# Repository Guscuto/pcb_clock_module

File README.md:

# pcb_clock_module
Clock Module PCB for 8 bit computer

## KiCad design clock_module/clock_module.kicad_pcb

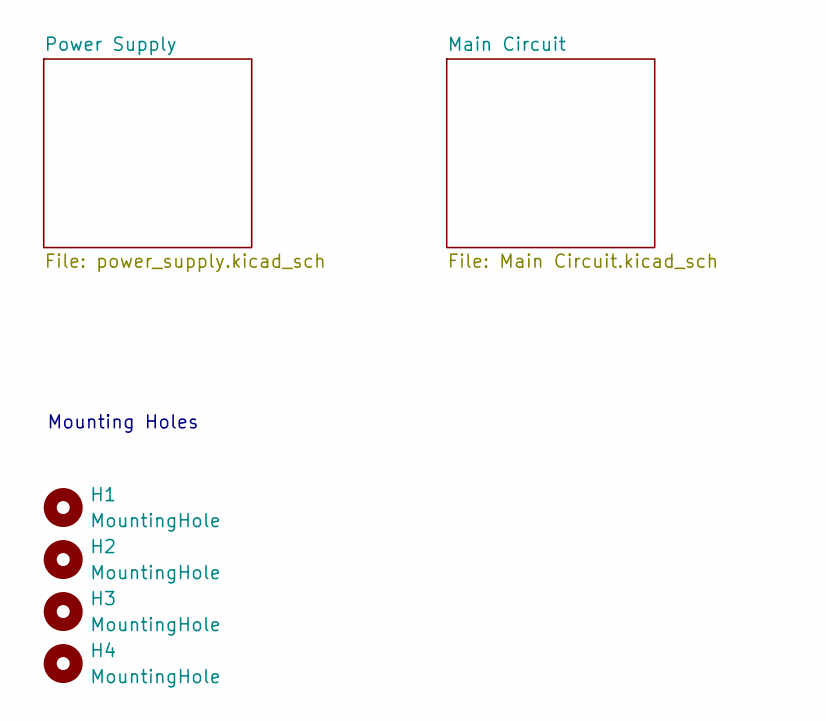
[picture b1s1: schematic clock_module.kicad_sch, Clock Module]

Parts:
H1, H2, H3, H4: MountingHole; MountingHole_3.2mm_M3

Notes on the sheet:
Mounting Holes

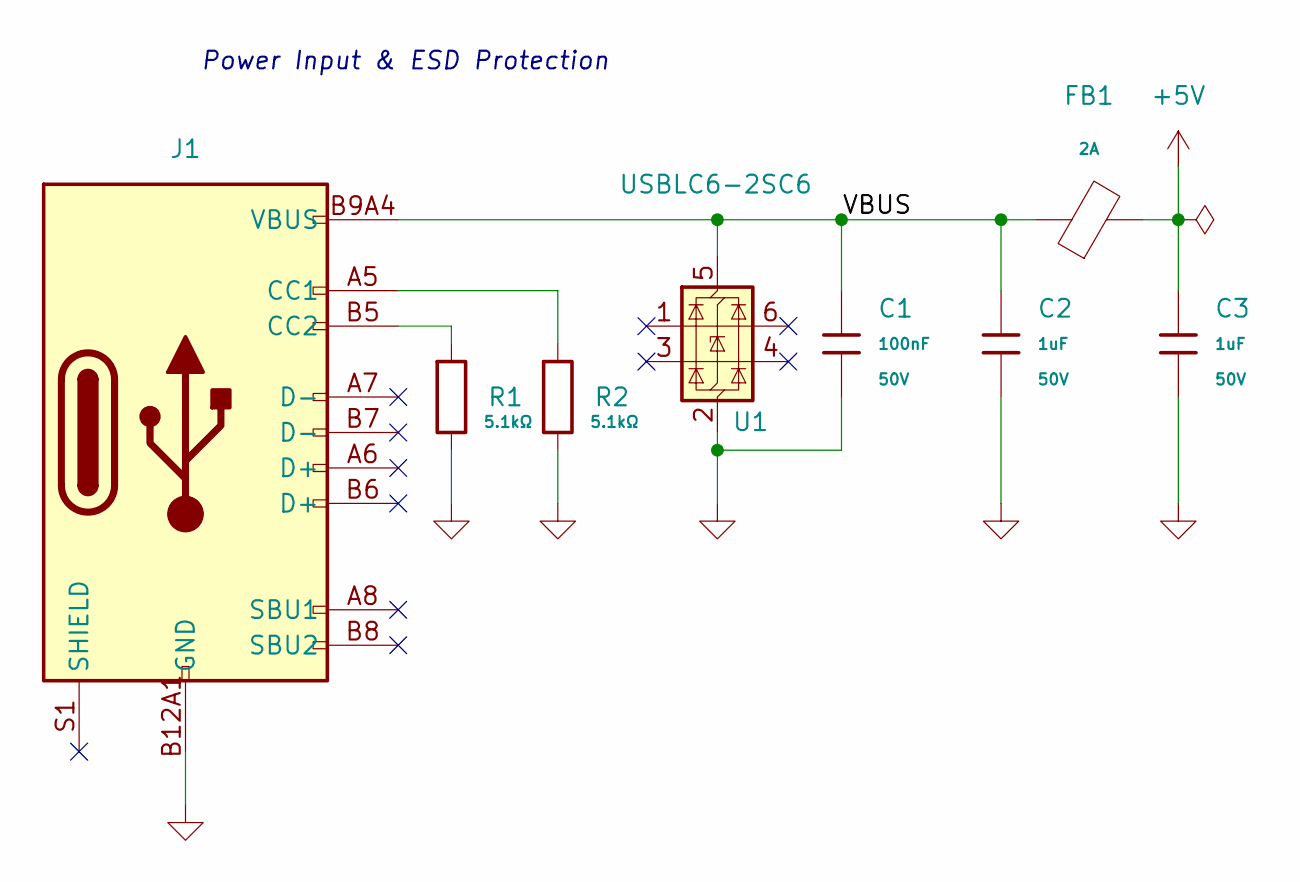
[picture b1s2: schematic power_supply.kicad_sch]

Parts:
C1: 100nF; C_0603; Voltage Rated 50V; Tolerance ±10%; Part CC0603KRX7R9BB104; LCSC C14663
C2, C3: 1uF; C_0603; Voltage Rated 50V; Tolerance ±10%; Part CL10A105KB8NNNC; LCSC C15849
FB1: FB_0603; Current Rating 2A; Tolerance ±25%; Part BLM18PG121SN1D; LCSC C14709
J1: Connector, USB-TYPE-C-16P; TYPE-C-SMD_HX-TYPE-C-16PIN; LCSC C2927039
R1, R2: 5.1kΩ; R_0603; Overload Voltage (Max) 75V; Tolerance ±1%; Part 0603WAF5101T5E; LCSC C23186
U1: USBLC6-2SC6; SOT-23-6; LCSC C7519

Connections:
+5V: C3.1, FB1.2; also elsewhere on the board
/Power Supply/VBUS: C1.1, C2.1, FB1.1, J1.A9B4 (VBUS), J1.B9A4 (VBUS), U1.5 (VBUS)
GND: C1.2, C2.2, C3.2, J1.A12B1 (GND), J1.B12A1 (GND), R1.2, R2.2, U1.2 (GND); also elsewhere on the board
unnamed: J1.A5 (CC1), R2.1
unnamed: J1.B5 (CC2), R1.1

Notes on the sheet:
Power Input & ESD Protection

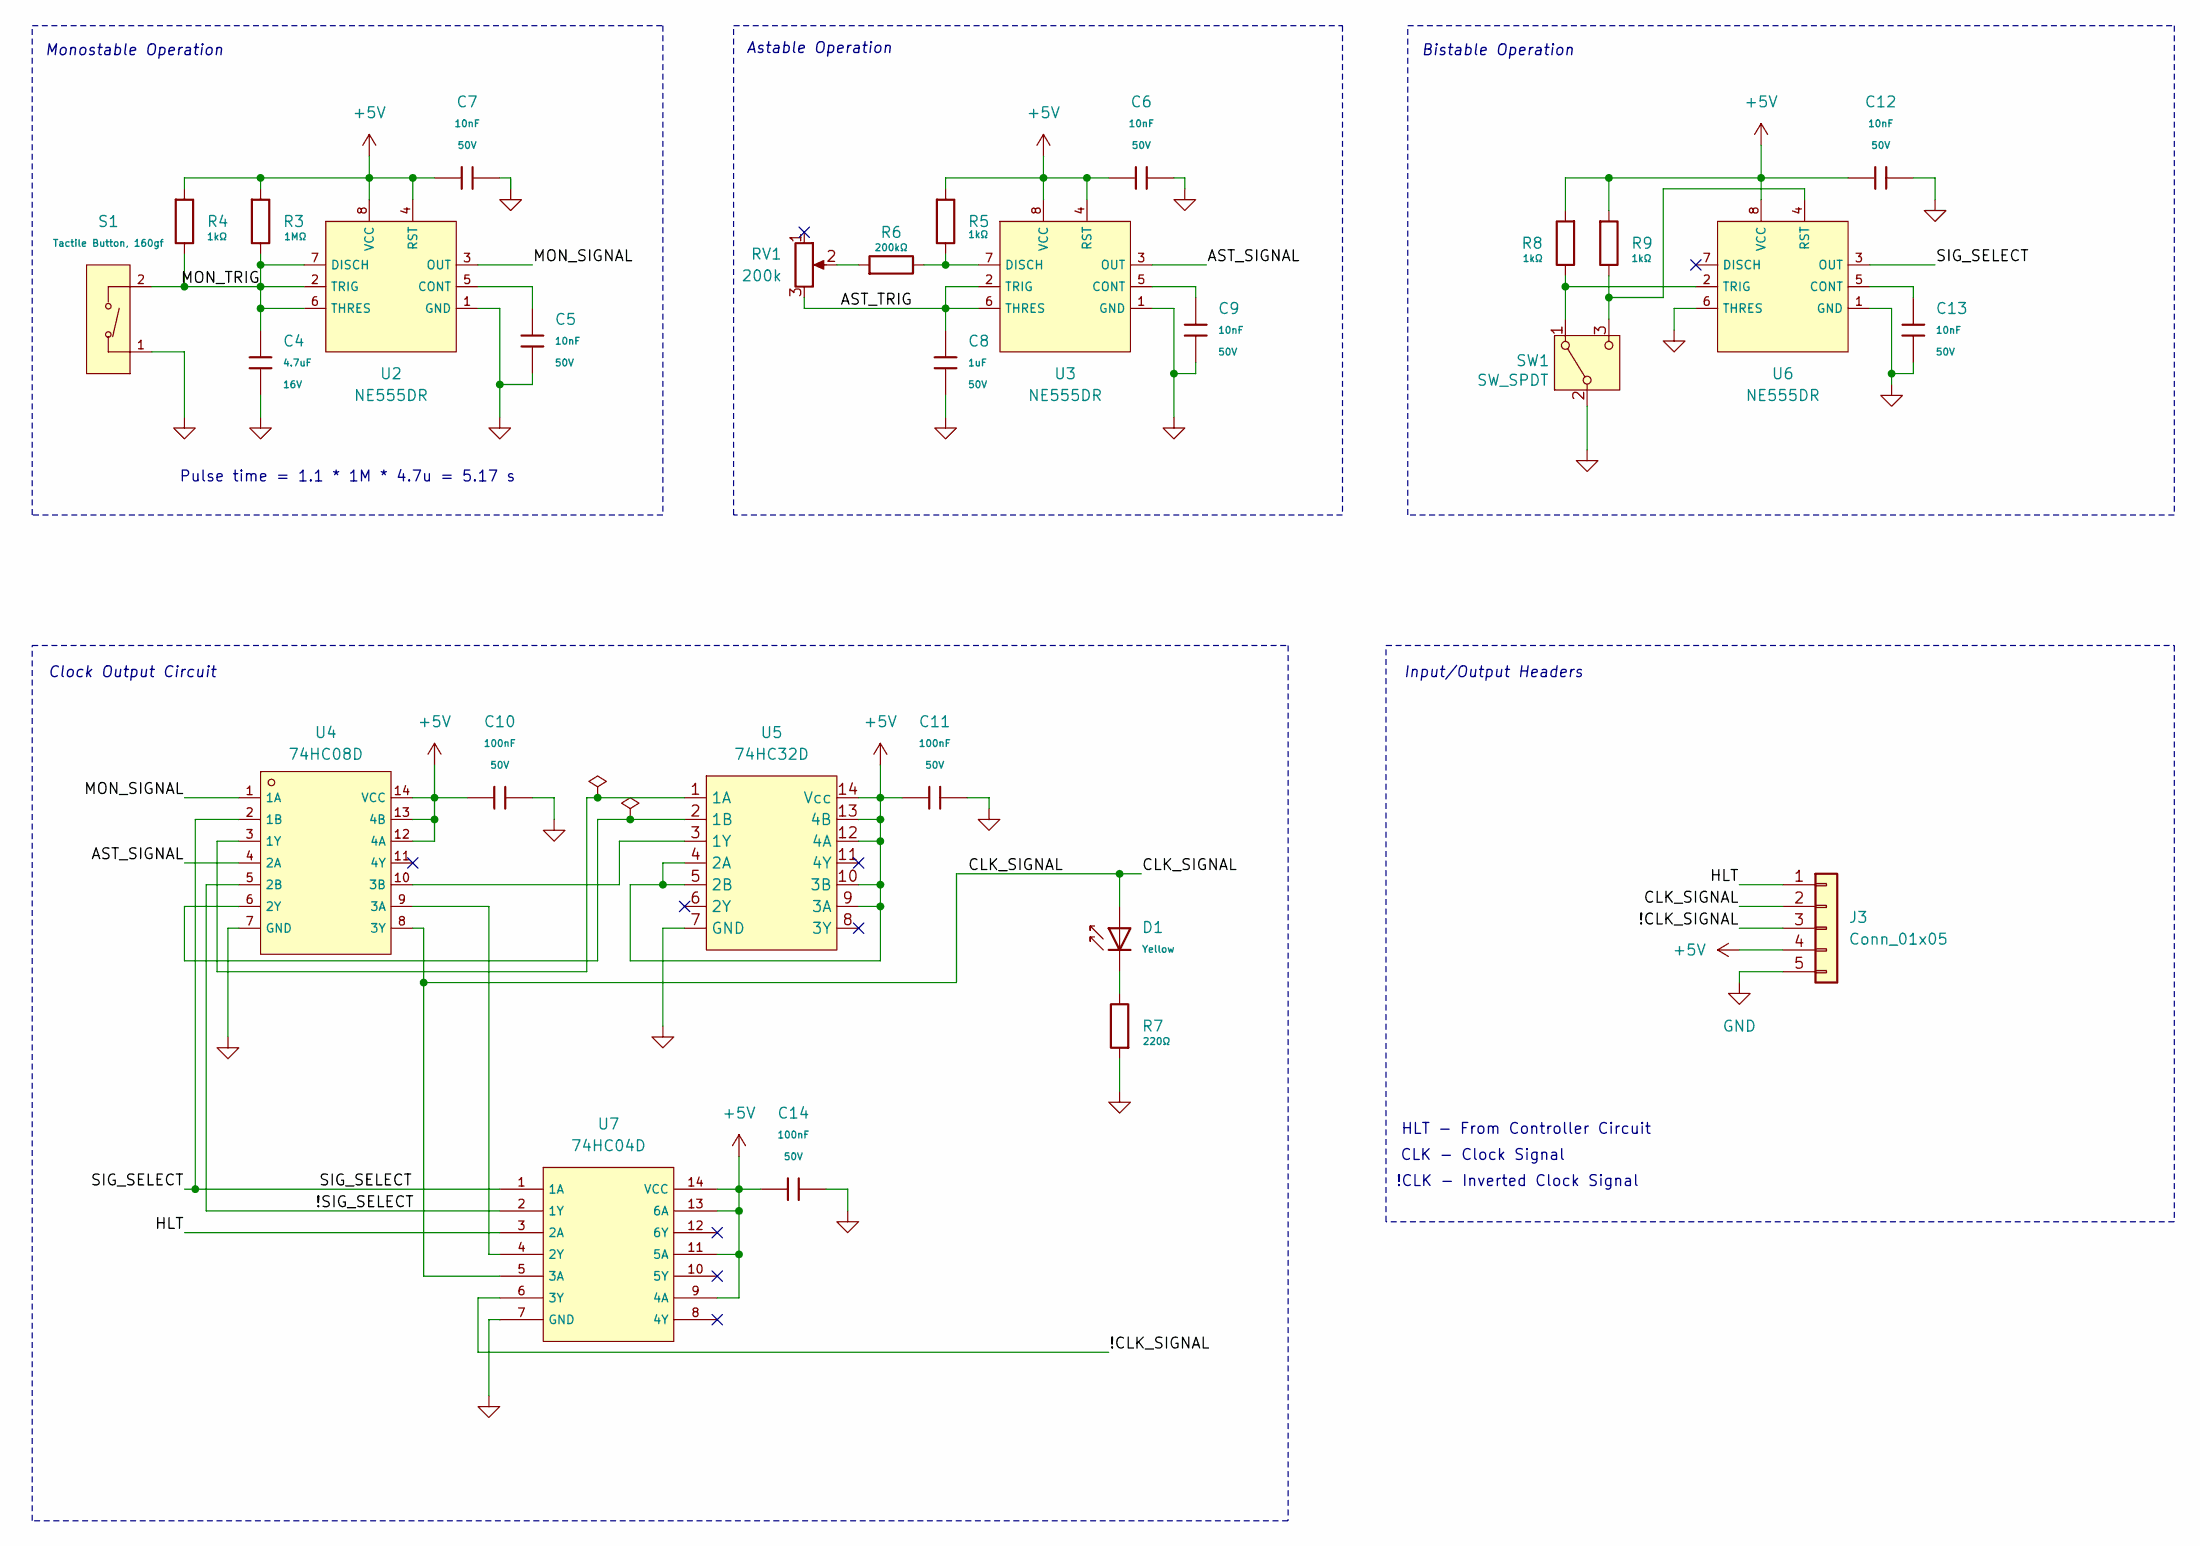
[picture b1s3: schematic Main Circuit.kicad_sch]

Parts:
C4: 4.7uF; C_0603; Voltage Rated 16V; Tolerance ±10%; Part CL10A475KO8NNNC; LCSC C19666
C5, C6, C7, C9, C12, C13: 10nF; C_0603; Voltage Rated 50V; Tolerance ±10%; Part 0603B103K500NT; LCSC C57112
C8: 1uF; C_0603; Voltage Rated 50V; Tolerance ±10%; Part CL10A105KB8NNNC; LCSC C15849
C10, C11, C14: 100nF; C_0603; Voltage Rated 50V; Tolerance ±10%; Part CC0603KRX7R9BB104; LCSC C14663
D1: Yellow; D_0603; Forward Voltage (VF) 1.6V~2.6V; Part NCD0603Y2; LCSC C89811
J3: Conn_01x05; PinHeader_1x05_P2.54mm_Vertical; LCSC C225480
R3: 1MΩ; R_0603; Overload Voltage (Max) 75V; Tolerance ±1%; Part 0603WAF1004T5E; LCSC C22935
R4, R5, R8, R9: 1kΩ; R_0603; Overload Voltage (Max) 75V; Tolerance ±1%; Part 0603WAF1001T5E; LCSC C21190
R6: 200kΩ; R_0603; Overload Voltage (Max) 75V; Tolerance ±1%; Part 0603WAF2003T5E; LCSC C25811
R7: 220Ω; R_0603; Overload Voltage (Max) 75V; Tolerance ±1%; Part 0603WAF2200T5E; LCSC C22962
RV1: 200k; Potentiometer_Bourns_3314G_Vertical; LCSC C3345207
S1: Tactile Button, 160gf; SW_TS-1088-AR02016; Voltage Rating (Dc) 12V; Part TS-1088-AR02016; LCSC C720477
SW1: SW_SPDT; SW_SPDT_L7.0mm_H16.0mm_W7.00mm; LCSC C7435557
U2, U3, U6: NE555DR; SOIC-8_L4.9-W3.9-P1.27-LS6.0-BL; Supply Voltage 4.5V~16V; Part NE555DR; LCSC C7593
U4: 74HC08D; SOIC-14_L8.7-W3.9-P1.27-LS6.0-BL; Supply Voltage 2V~6V; Part 74HC08D,653; LCSC C5593
U5: 74HC32D; SOIC-14_L8.7-W3.9-P1.27-LS6.0-BL; LCSC C6838
U7: 74HC04D; SOIC-14_L8.7-W3.9-P1.27-LS6.0-BL; Supply Voltage(Single) 2V~6V; Part 74HC04D,653; LCSC C5590

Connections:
+5V: C6.1, C7.1, C10.1, C11.1, C12.1, C14.1, J3.4, R3.1, R4.1, R5.1, R8.1, R9.1, U2.4 (RST), U2.8 (VCC), U3.4 (RST), U3.8 (VCC), U4.12 (4A), U4.13 (4B), U4.14 (VCC), U5.4 (2A), U5.5 (2B), U5.9 (3A), U5.10 (3B), U5.12 (4A), U5.13 (4B), U5.14 (Vcc), U6.8 (VCC), U7.9 (4A), U7.11 (5A), U7.13 (6A), U7.14 (VCC); also elsewhere on the board
/Main Circuit/!CLK_SIGNAL: J3.3, U7.6 (3Y)
/Main Circuit/!SIG_SELECT: U4.5 (2B), U7.2 (1Y)
/Main Circuit/AST_SIGNAL: U3.3 (OUT), U4.4 (2A)
/Main Circuit/AST_TRIG: C8.1, RV1.3, U3.2 (TRIG), U3.6 (THRES)
/Main Circuit/CLK_SIGNAL: D1.2, J3.2, U4.8 (3Y), U7.5 (3A)
/Main Circuit/HLT: J3.1, U7.3 (2A)
/Main Circuit/MON_SIGNAL: U2.3 (OUT), U4.1 (1A)
/Main Circuit/MON_TRIG: C4.1, R3.2, R4.2, S1.2 (B), U2.2 (TRIG), U2.6 (THRES), U2.7 (DISCH)
/Main Circuit/SIG_SELECT: U4.2 (1B), U6.3 (OUT), U7.1 (1A)
GND: C4.2, C5.2, C6.2, C7.2, C8.2, C9.2, C10.2, C11.2, C12.2, C13.2, C14.2, J3.5, R7.1, S1.1 (A), SW1.2 (B), U2.1 (GND), U3.1 (GND), U4.7 (GND), U5.7 (GND), U6.1 (GND), U6.6 (THRES), U7.7 (GND); also elsewhere on the board
unnamed: D1.1, R7.2
unnamed: R6.1, RV1.2
unnamed: R8.2, SW1.1 (A), U6.2 (TRIG)
unnamed: R9.2, SW1.3 (C), U6.4 (RST)
unnamed: C5.1, U2.5 (CONT)
unnamed: C9.1, U3.5 (CONT)
unnamed: R5.2, R6.2, U3.7 (DISCH)
unnamed: U4.3 (1Y), U5.1 (1A)
unnamed: U4.6 (2Y), U5.2 (1B)
unnamed: U4.9 (3A), U7.4 (2Y)
unnamed: U4.10 (3B), U5.3 (1Y)
unnamed: C13.1, U6.5 (CONT)

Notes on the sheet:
Bistable Operation
Pulse time = 1.1 * 1M * 4.7u = 5.17 s
Astable Operation
!CLK - Inverted Clock Signal
Clock Output Circuit
CLK - Clock Signal
Input/Output Headers
Monostable Operation
HLT - From Controller Circuit

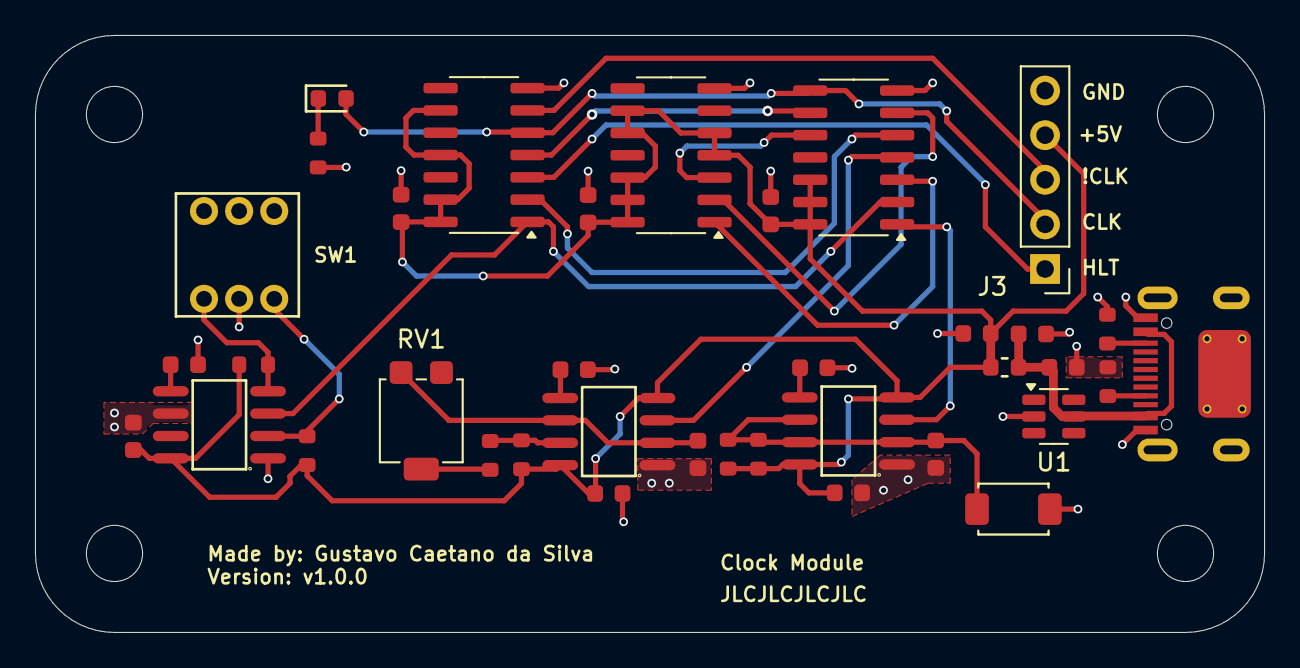
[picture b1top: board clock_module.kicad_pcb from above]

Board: 4 copper layers, 70.0 x 34.0 mm, 41 parts (0 on the bottom side), 26 nets.

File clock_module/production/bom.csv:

Designator,Footprint,Quantity,Value,LCSC Part #
"C1, C10, C11, C14",C_0603,4,100nF,C14663
"C12, C13, C5, C6, C7, C9",C_0603,6,10nF,C57112
"C2, C3, C8",C_0603,3,1uF,C15849
C4,C_0603,1,4.7uF,C19666
D1,D_0603,1,Yellow,C89811
FB1,FB_0603,1,~,C14709
J1,TYPE-C-SMD_HX-TYPE-C-16PIN,1,"Connector, USB-TYPE-C-16P",C2927039
J3,PinHeader_1x05_P2.54mm_Vertical,1,Conn_01x05,C225480
"R1, R2",R_0603,2,5.1kΩ,C23186
R3,R_0603,1,1MΩ,C22935
"R4, R5, R8, R9",R_0603,4,1kΩ,C21190
R6,R_0603,1,200kΩ,C25811
R7,R_0603,1,220Ω,C22962
RV1,Potentiometer_Bourns_3314G_Vertical,1,200k,C3345207
S1,SW_TS-1088-AR02016,1,"Tactile Button, 160gf",C720477
SW1,SW_SPDT_L7.0mm_H16.0mm_W7.00mm,1,SW_SPDT,C7435557
U1,SOT-23-6,1,USBLC6-2SC6,C7519
"U2, U3, U6",SOIC-8_L4.9-W3.9-P1.27-LS6.0-BL,3,NE555DR,C7593
U4,SOIC-14_L8.7-W3.9-P1.27-LS6.0-BL,1,74HC08D,C5593
U5,SOIC-14_L8.7-W3.9-P1.27-LS6.0-BL,1,74HC32D,C6838
U7,SOIC-14_L8.7-W3.9-P1.27-LS6.0-BL,1,74HC04D,C5590

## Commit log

2026-05-18 add: monostable operation circuit
2026-05-21 add: astable circuit
2026-05-26 pcb routes (unfinished)
2026-05-27 finished board
2026-05-31 final v1.0.0 project
